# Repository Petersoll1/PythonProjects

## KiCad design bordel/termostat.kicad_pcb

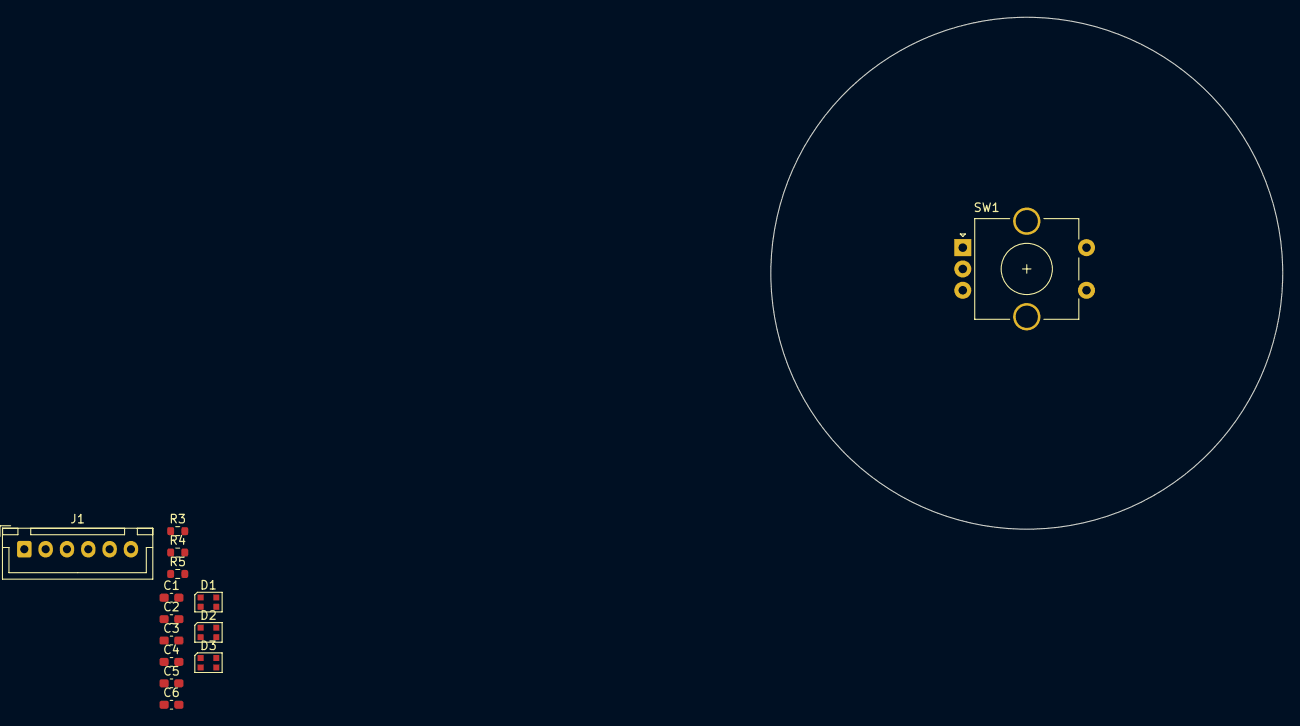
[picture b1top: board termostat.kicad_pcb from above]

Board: 2 copper layers, 60.0 x 60.0 mm, 14 parts (0 on the bottom side), 5 nets, no tracks yet.

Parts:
C1, C2, C3, C4, C5, C6: C; C_0603_1608Metric_Pad1.08x0.95mm_HandSolder
D1, D2, D3: WS2812B-2020; LED_WS2812B-2020_PLCC4_2.0x2.0mm
J1: Conn_01x06; JST_XH_B6B-XH-A_1x06_P2.50mm_Vertical
R3, R4, R5: 10k; R_0603_1608Metric
SW1: RotaryEncoder_Switch_MP; RotaryEncoder_Alps_EC11E-Switch_Vertical_H20mm_CircularMoun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

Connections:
+3.3V: C1.1, C2.1, C2.2, C3.1, C3.2, C4.1, C5.1, C6.1, D1.4 (VDD), D2.4 (VDD), D3.4 (VDD), R4.1, R5.1, SW1.A, SW1.B, SW1.C, SW1.S1
GND: C4.2, C5.2, C6.2, D1.2 (VSS), D2.2 (VSS), D3.2 (VSS), R3.2, R4.2, R5.2, SW1.MP
unnamed: C1.2, R3.1, SW1.S2
unnamed: D1.1 (DOUT), D2.3 (DIN)
unnamed: D2.1 (DOUT), D3.3 (DIN)

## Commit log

2025-10-03 prvni commit
2025-10-03 druhy commit
2025-10-10 druhy commity
2025-10-31 asi treti commit? fakt netusim
2025-11-07 ctvrty commit. stringy a seznam
2025-11-14 paty commit. seznamy
2025-11-21 sesty commit. pokracovani v prikladech seznamu
2026-02-13 funkce
